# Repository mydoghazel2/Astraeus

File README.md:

# Astraeus

This is the github repo of an SRAD avionics project named Astraeus.

Astreaus is a student led project to develop cheap, open-source, and modular avionics. The goal is to create electronics for our competition rocket and for student use on personal rockets. 

Astraeus is the greek god of the wind and dusk

# Final Design 
## Top Side

## Bottom Side 

# PCB

EAGLE is used as the PCB designing software. All the libraries needed is included in `./PCB/lib`

- if you are on linux. Use the following command to make a sim links to the default eagle save directory  

```
cd ~/EAGLE/projects
ln -s ~/Projects/Astraeus/PCB/ git-pcb
```

- if you are on windows 10: Add instructions on how to get EAGLE running

# TO-DO

- [x] Initial planning and requirement gathering.
- [x] Finalizing the hardware specification.
- [x] Schematic design
  - [x] BMS
  - [x] voltage regulation
  - [x] Sensors
  - [x] USB
  - [ ] upload/download
  - [ ] SD card

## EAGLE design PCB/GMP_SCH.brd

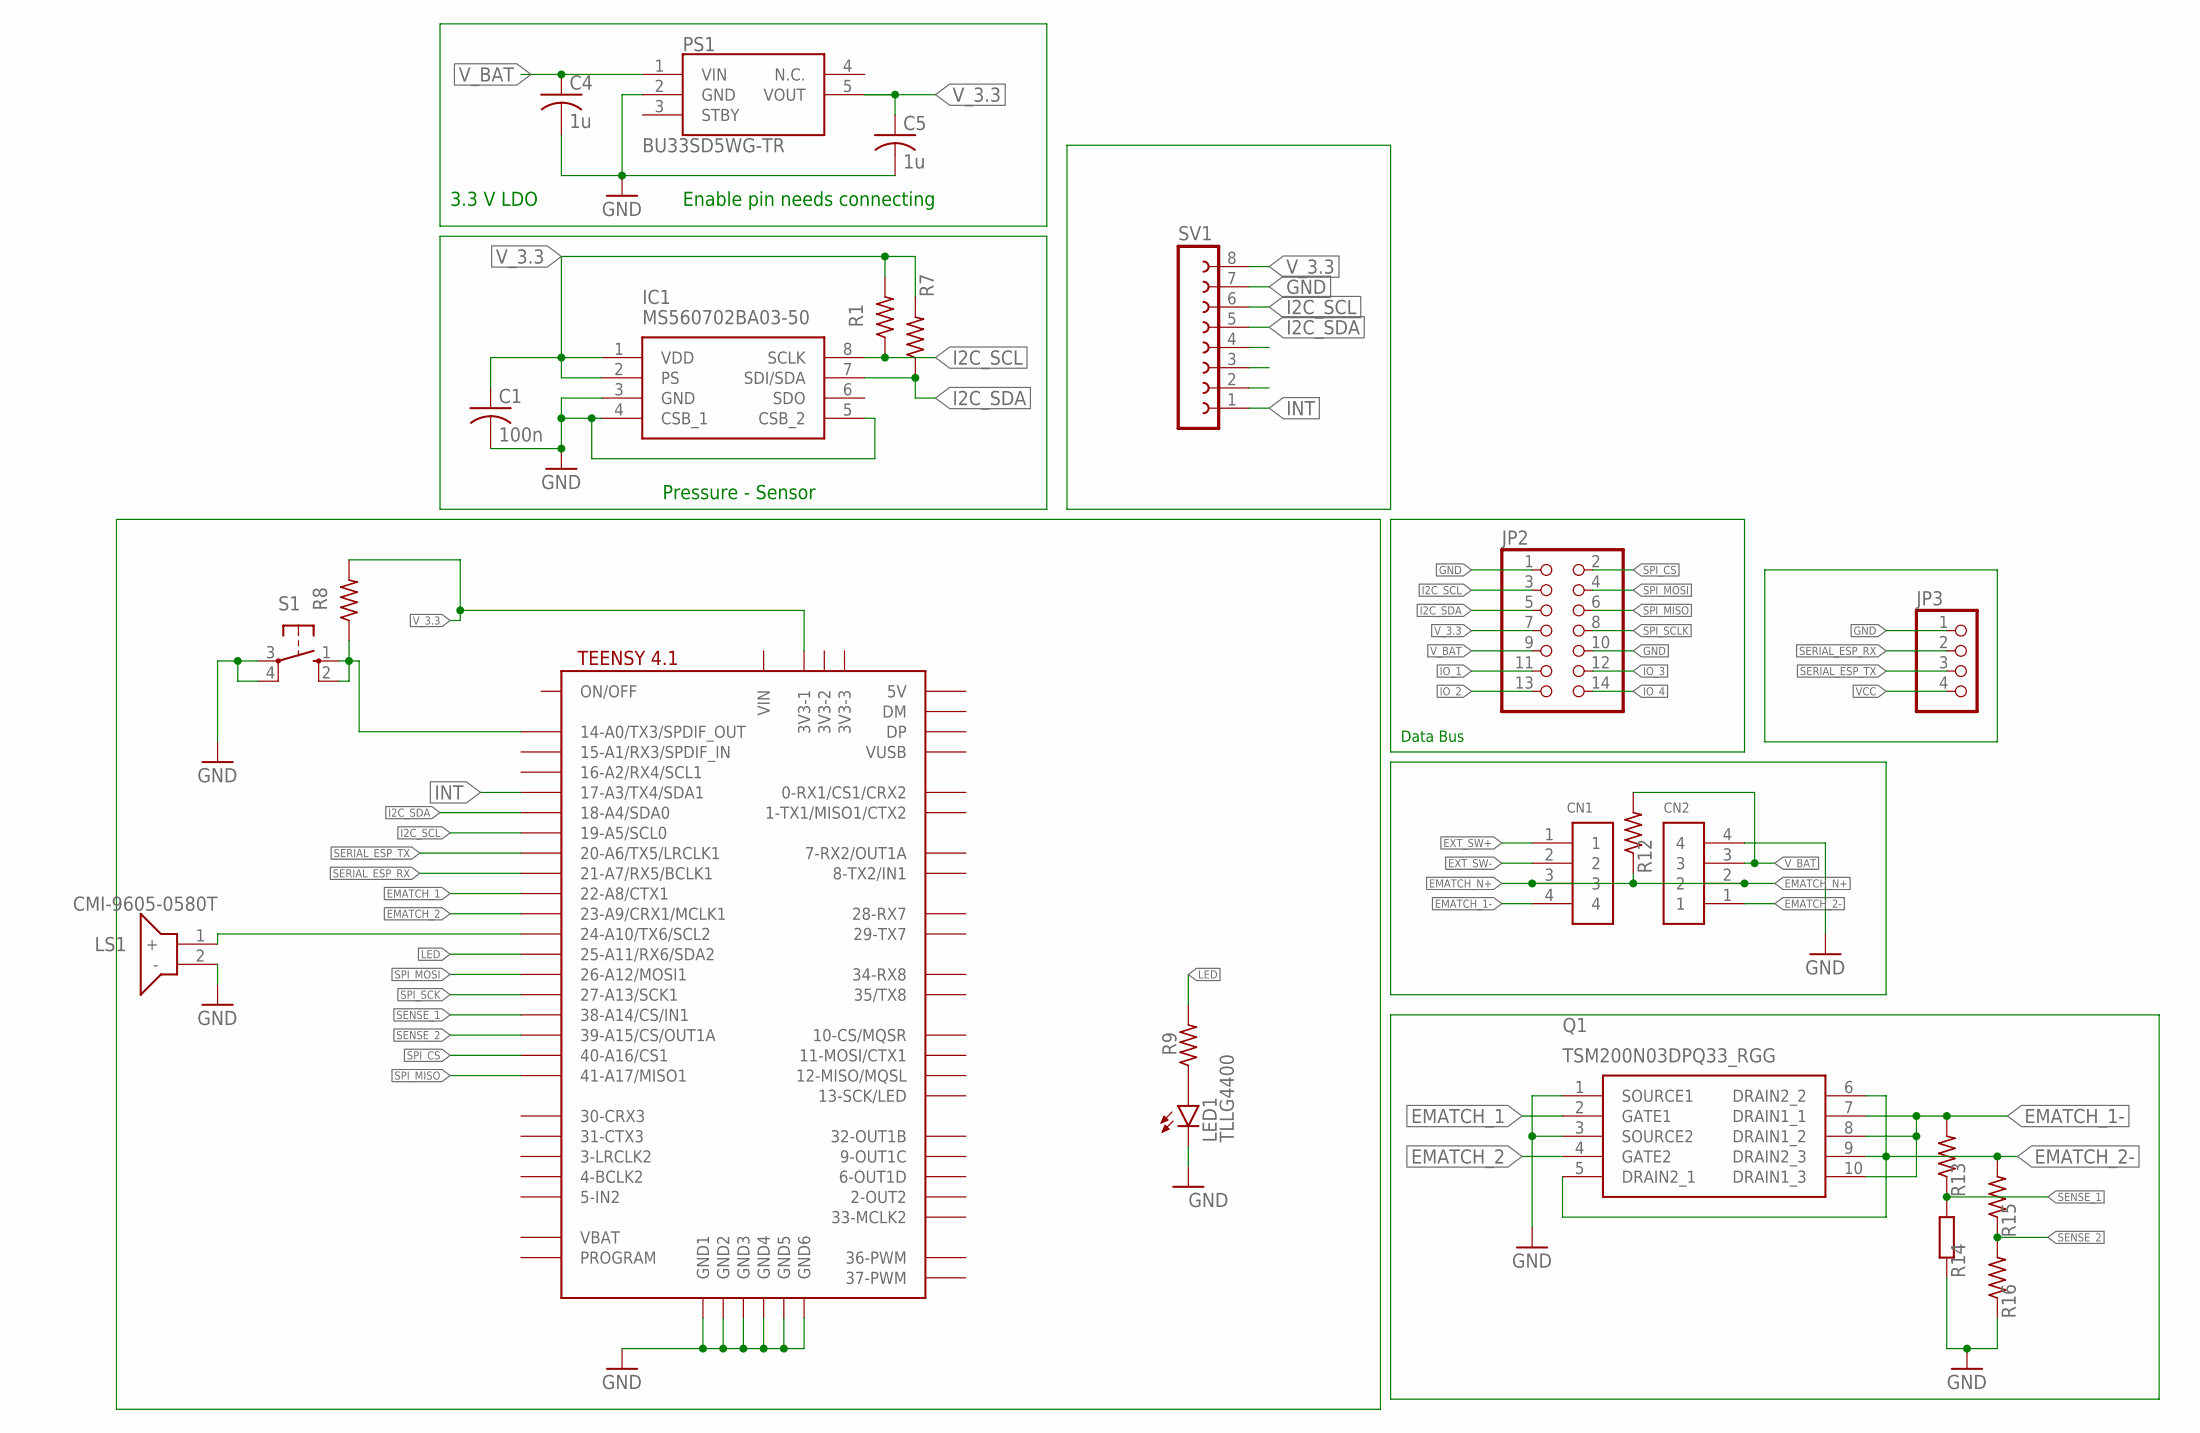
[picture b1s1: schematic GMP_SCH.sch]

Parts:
C1: 100n; C0805
C4, C5: 1u; C0805
CN1, CN2: 1X4-3.5MM; 1X04-3.5MM
IC1: MS560702BA03-50; MS5607-02BA03
JP2: PINHD-2X7; 2X07
JP3: PINHD-1X4/90; 1X04/90
LED1: TLLG4400; LED3MM
LS1: CMI-9605-0580T; CMI96050580T
PS1: BU33SD5WG-TR; SOT95P280X125-5N
Q1: TSM200N03DPQ33_RGG; TSM200N03DPQ33RGG
R1, R7, R8: 10k; 0805-THM
R9: 2k; 0805-THM
R12: 0; 0805-THM
R13, R15: 100k; 0805-THM
R14: 27k; 0207/12
R16: 27k; 0805-THM
S1: 10-XX; B3F-10XX
SV1: FE08-1; FE08
U$1: TEENSY41-E; TENNSY41-E

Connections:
EMATCH_1: Q1.2 (GATE1), U$1.22-A8/CTX1
EMATCH_1-: CN1.4, Q1.7 (DRAIN1_1), Q1.8 (DRAIN1_2), Q1.10 (DRAIN1_3), R13.2
EMATCH_2: Q1.4 (GATE2), U$1.23-A9/CRX1/MCLK1
EMATCH_2-: CN2.1, Q1.5 (DRAIN2_1), Q1.6 (DRAIN2_2), Q1.9 (DRAIN2_3), R15.2
EMATCH_N+: CN1.3, CN2.2, R12.1
EXT_SW+: CN1.1
EXT_SW-: CN1.2
GND: C1.2, C4.2, C5.2, CN2.4, IC1.3 (GND), IC1.4 (CSB_1), IC1.5 (CSB_2), JP2.1, JP2.10, JP3.1, LED1.K (C), LS1.2 (-), PS1.2 (GND), Q1.1 (SOURCE1), Q1.3 (SOURCE2), R14.1, R16.1, S1.3, S1.4 (P1), SV1.7, U$1.GND1, U$1.GND2, U$1.GND3, U$1.GND4, U$1.GND5, U$1.GND6
I2C_SCL: IC1.8 (SCLK), JP2.3, R1.1, SV1.6, U$1.19-A5/SCL0
I2C_SDA: IC1.7 (SDI/SDA), JP2.5, R7.1, SV1.5, U$1.18-A4/SDA0
INT: SV1.1, U$1.17-A3/TX4/SDA1, U$1.30-CRX3
IO_1: JP2.11
IO_2: JP2.13
IO_3: JP2.12
IO_4: JP2.14
LED: R9.2, U$1.25-A11/RX6/SDA2
unnamed: LED1.A, R9.1
unnamed: LS1.1 (+), U$1.24-A10/TX6/SCL2
unnamed: R8.1, S1.1 (S), S1.2 (S1), U$1.14-A0/TX3/SPDIF_OUT
SENSE_1: R13.1, R14.2, U$1.38-A14/CS/IN1
SENSE_2: R15.1, R16.2, U$1.39-A15/CS/OUT1A
SERIAL_ESP_RX: JP3.2, U$1.21-A7/RX5/BCLK1
SERIAL_ESP_TX: JP3.3, U$1.20-A6/TX5/LRCLK1
SPI_CS: JP2.2, U$1.40-A16/CS1
SPI_MISO: JP2.6, U$1.41-A17/MISO1
SPI_MOSI: JP2.4, U$1.26-A12/MOSI1
SPI_SCK: U$1.27-A13/SCK1
SPI_SCLK: JP2.8
VCC: JP3.4
V_3.3: C1.1, C5.1, IC1.1 (VDD), IC1.2 (PS), JP2.7, PS1.5 (VOUT), R1.2, R7.2, R8.2, SV1.8, U$1.3V3-1
V_BAT: C4.1, CN2.3, JP2.9, PS1.1 (VIN), R12.2

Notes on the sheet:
Pressure - Sensor
Enable pin needs connecting
3.3 V LDO
Data Bus

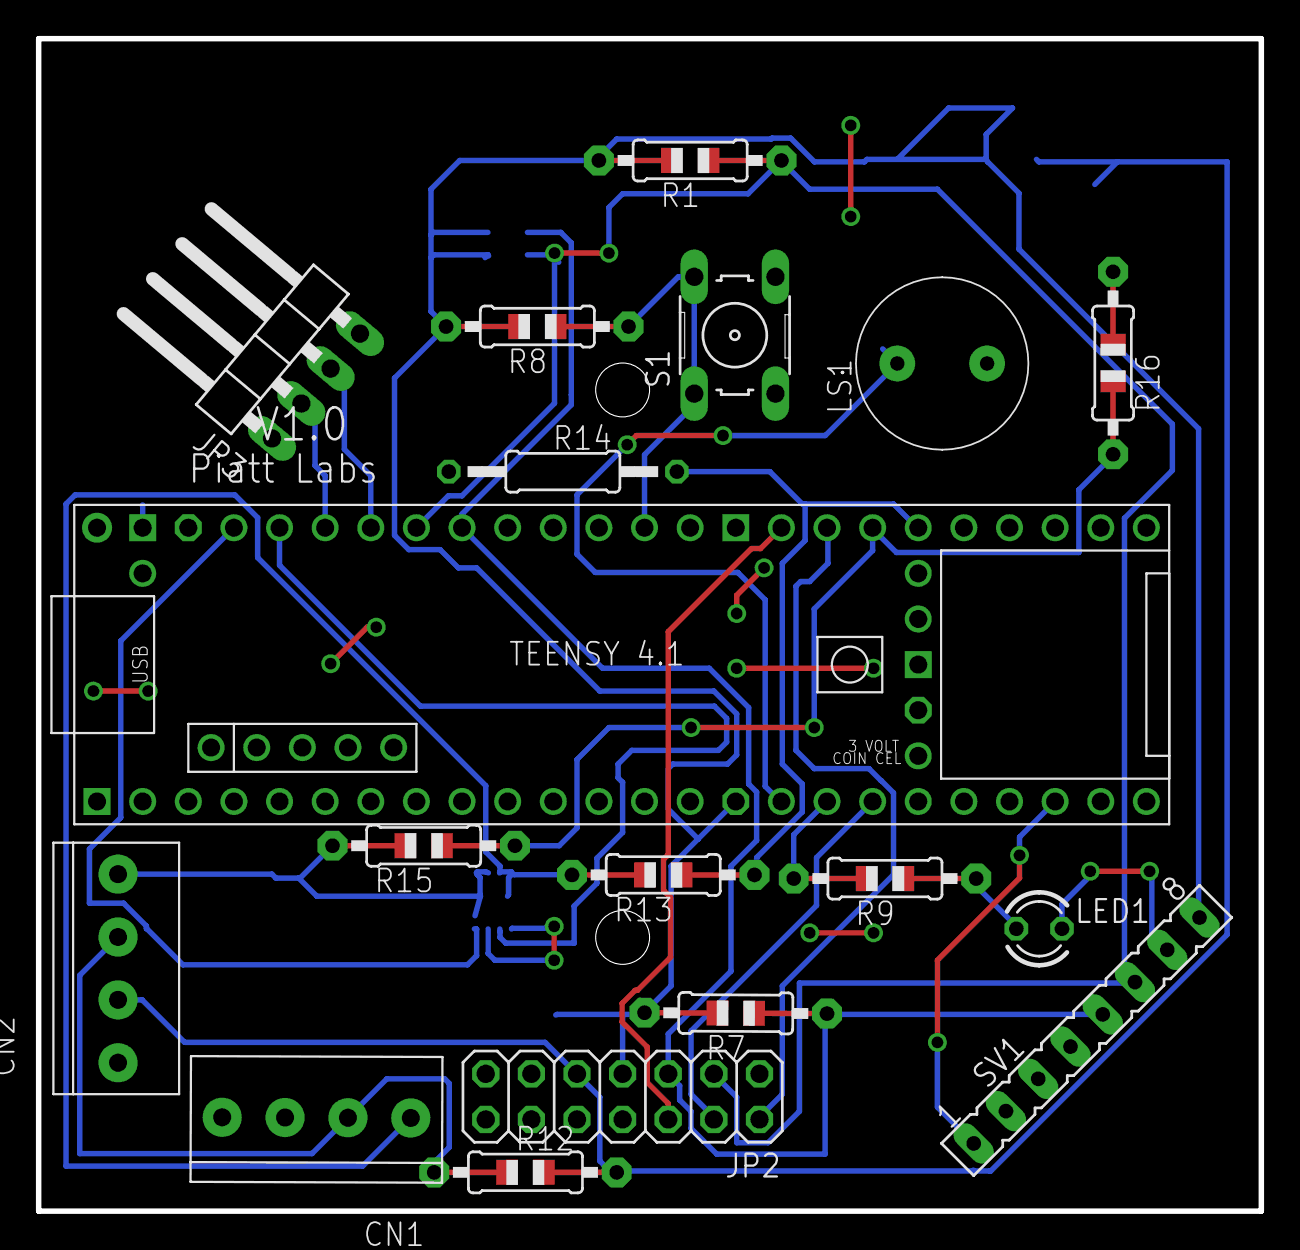
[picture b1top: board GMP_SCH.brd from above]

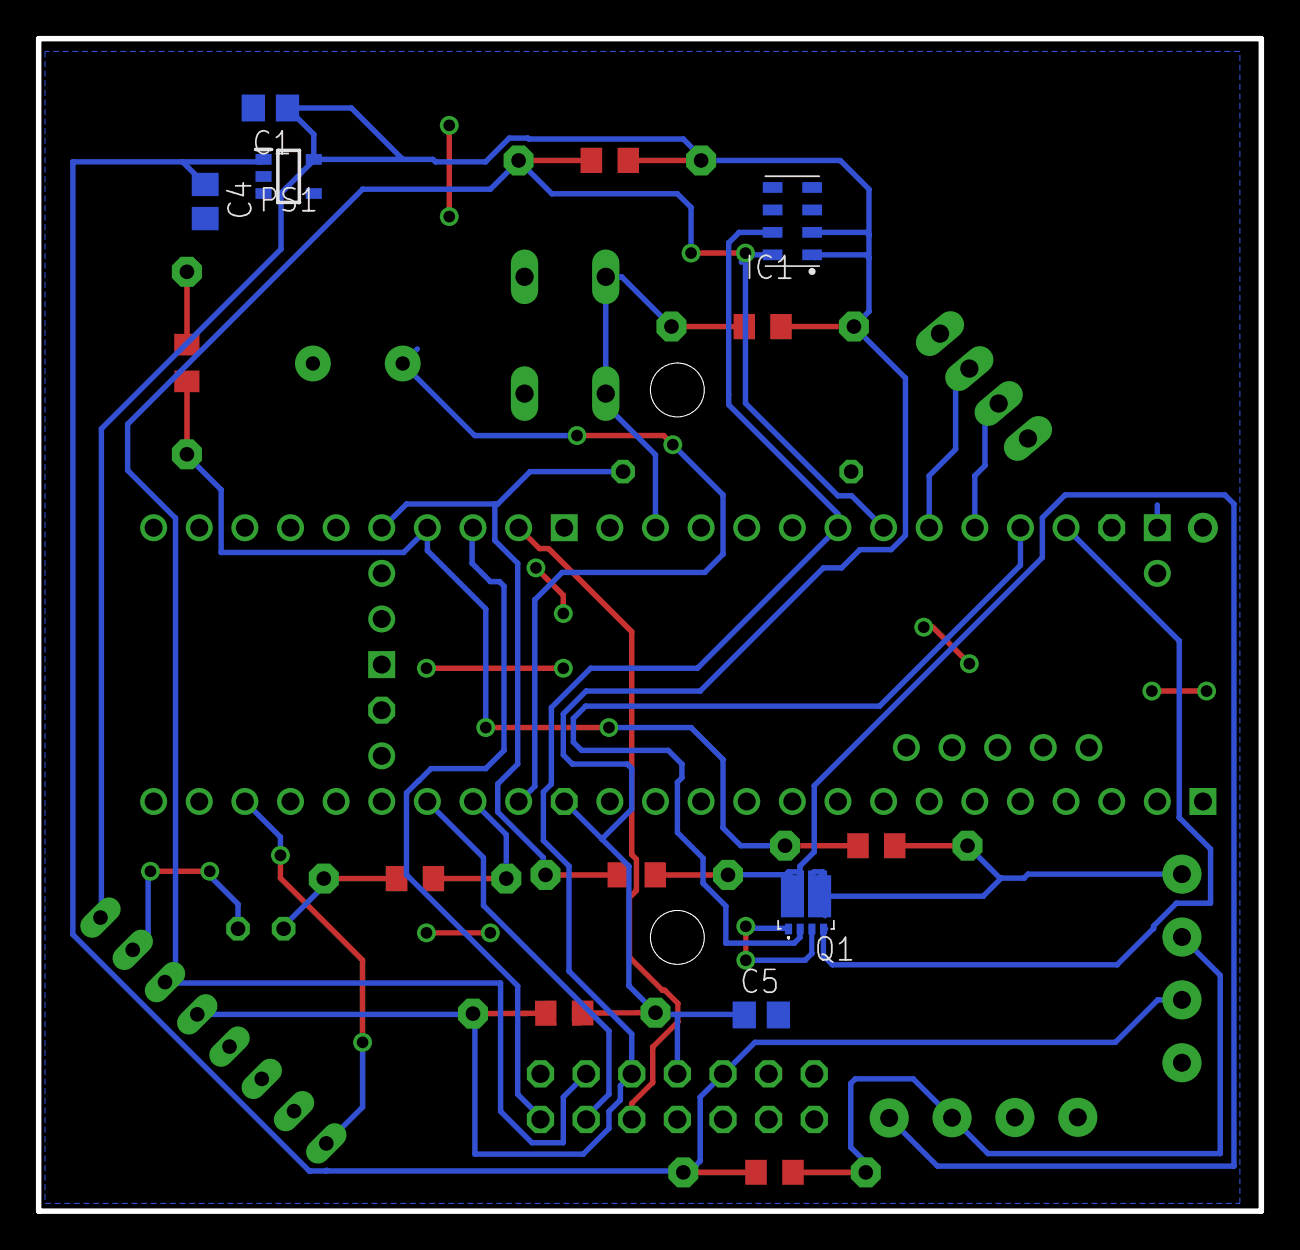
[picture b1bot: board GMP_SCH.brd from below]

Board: 2 copper layers, 68.1 x 65.3 mm, 24 parts (6 on the bottom side), 22 nets.

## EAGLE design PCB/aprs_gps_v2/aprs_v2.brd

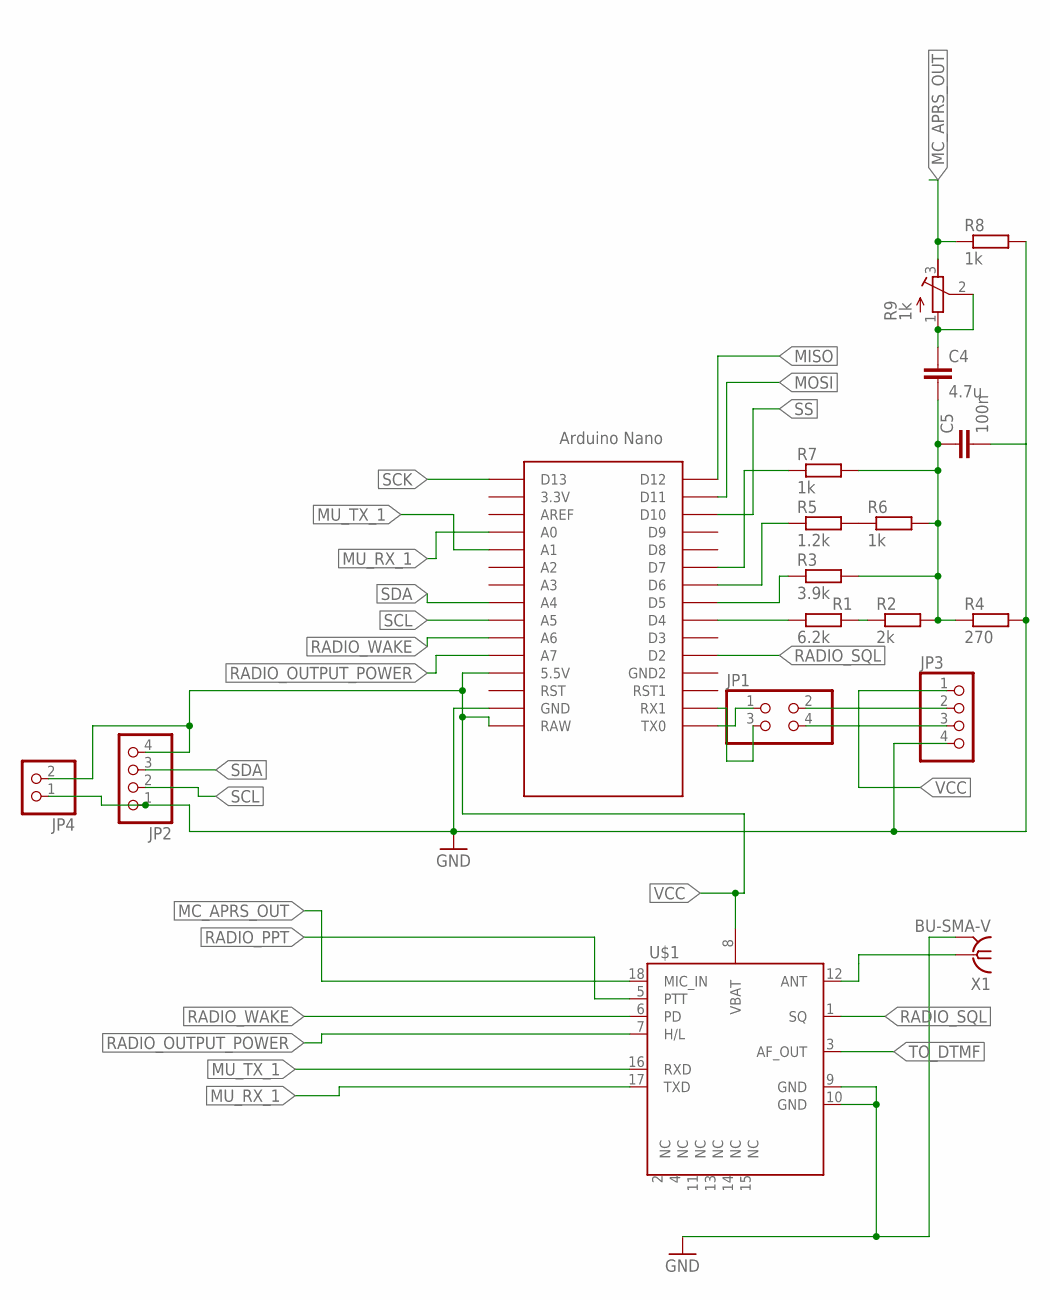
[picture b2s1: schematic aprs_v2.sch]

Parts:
C4: 4.7u; C1206
C5: 100n; C0805
JP1: PINHD-2X2; 2X02
JP2, JP3: PINHD-1X4; 1X04
JP4: PINHD-1X2; 1X02
R1: 6.2k; 0207/7
R2: 2k; 0207/7
R3: 3.9k; 0207/7
R4: 270; 0204/7
R5: 1.2k; 0207/7
R6: 1k; 0207/7
R7: 1k; 0204/5
R8: 1k; 0207/12
R9: 1k; RTRIM3339P
U$1: DRA818A
U$2: NANO
X1: BU-SMA-V

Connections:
GND: C5.2, JP2.1, JP3.4, JP4.1, R4.2, R8.2, U$1.9 (GND), U$1.10 (GND), U$2.GND, X1.2, X1.3 (2), X1.4 (2), X1.5 (2)
MC_APRS_OUT: R8.1, R9.3 (E), U$1.18 (MIC_IN)
MISO: U$2.D12
MOSI: U$2.D11
MU_RX_1: U$1.17 (TXD), U$2.A0
MU_TX_1: U$1.16 (RXD), U$2.A1
unnamed: U$1.12 (ANT), X1.1
unnamed: JP1.1, U$2.TX0
unnamed: JP1.2, JP3.2
unnamed: R1.1, U$2.D4
unnamed: R3.1, U$2.D5
unnamed: R5.1, U$2.D6
unnamed: R7.1, U$2.D7
unnamed: R1.2, R2.1
unnamed: R5.2, R6.1
unnamed: C4.2, C5.1, R2.2, R3.2, R4.1, R6.2, R7.2
unnamed: C4.1, R9.1 (A), R9.2 (S)
unnamed: JP1.3, U$2.RX1
unnamed: JP1.4, JP3.3
RADIO_OUTPUT_POWER: U$1.7 (H/L), U$2.A7
RADIO_PPT: U$1.5 (PTT)
RADIO_SQL: U$1.1 (SQ), U$2.D2
RADIO_WAKE: U$1.6 (PD), U$2.A6
SCK: U$2.D13
SCL: JP2.2, U$2.A5
SDA: JP2.3, U$2.A4
SS: U$2.D10
TO_DTMF: U$1.3 (AF_OUT)
VCC: JP2.4, JP3.1, JP4.2, U$1.8 (VBAT), U$2.5V (5.5V), U$2.RAW

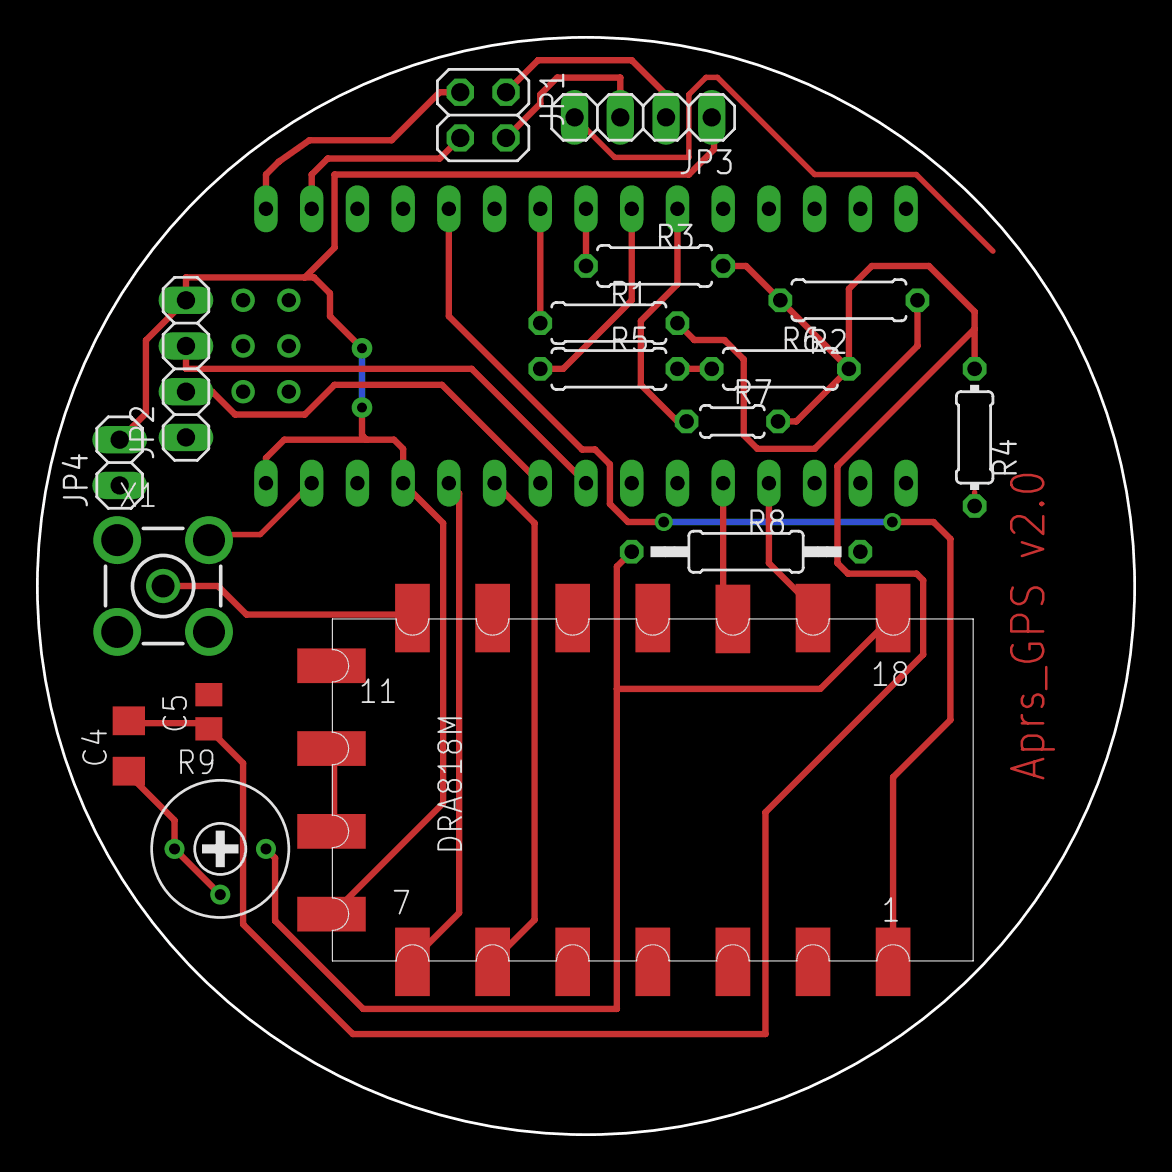
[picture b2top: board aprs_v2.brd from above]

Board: 2 copper layers, 61.0 x 61.0 mm, 18 parts (1 on the bottom side), 23 nets.

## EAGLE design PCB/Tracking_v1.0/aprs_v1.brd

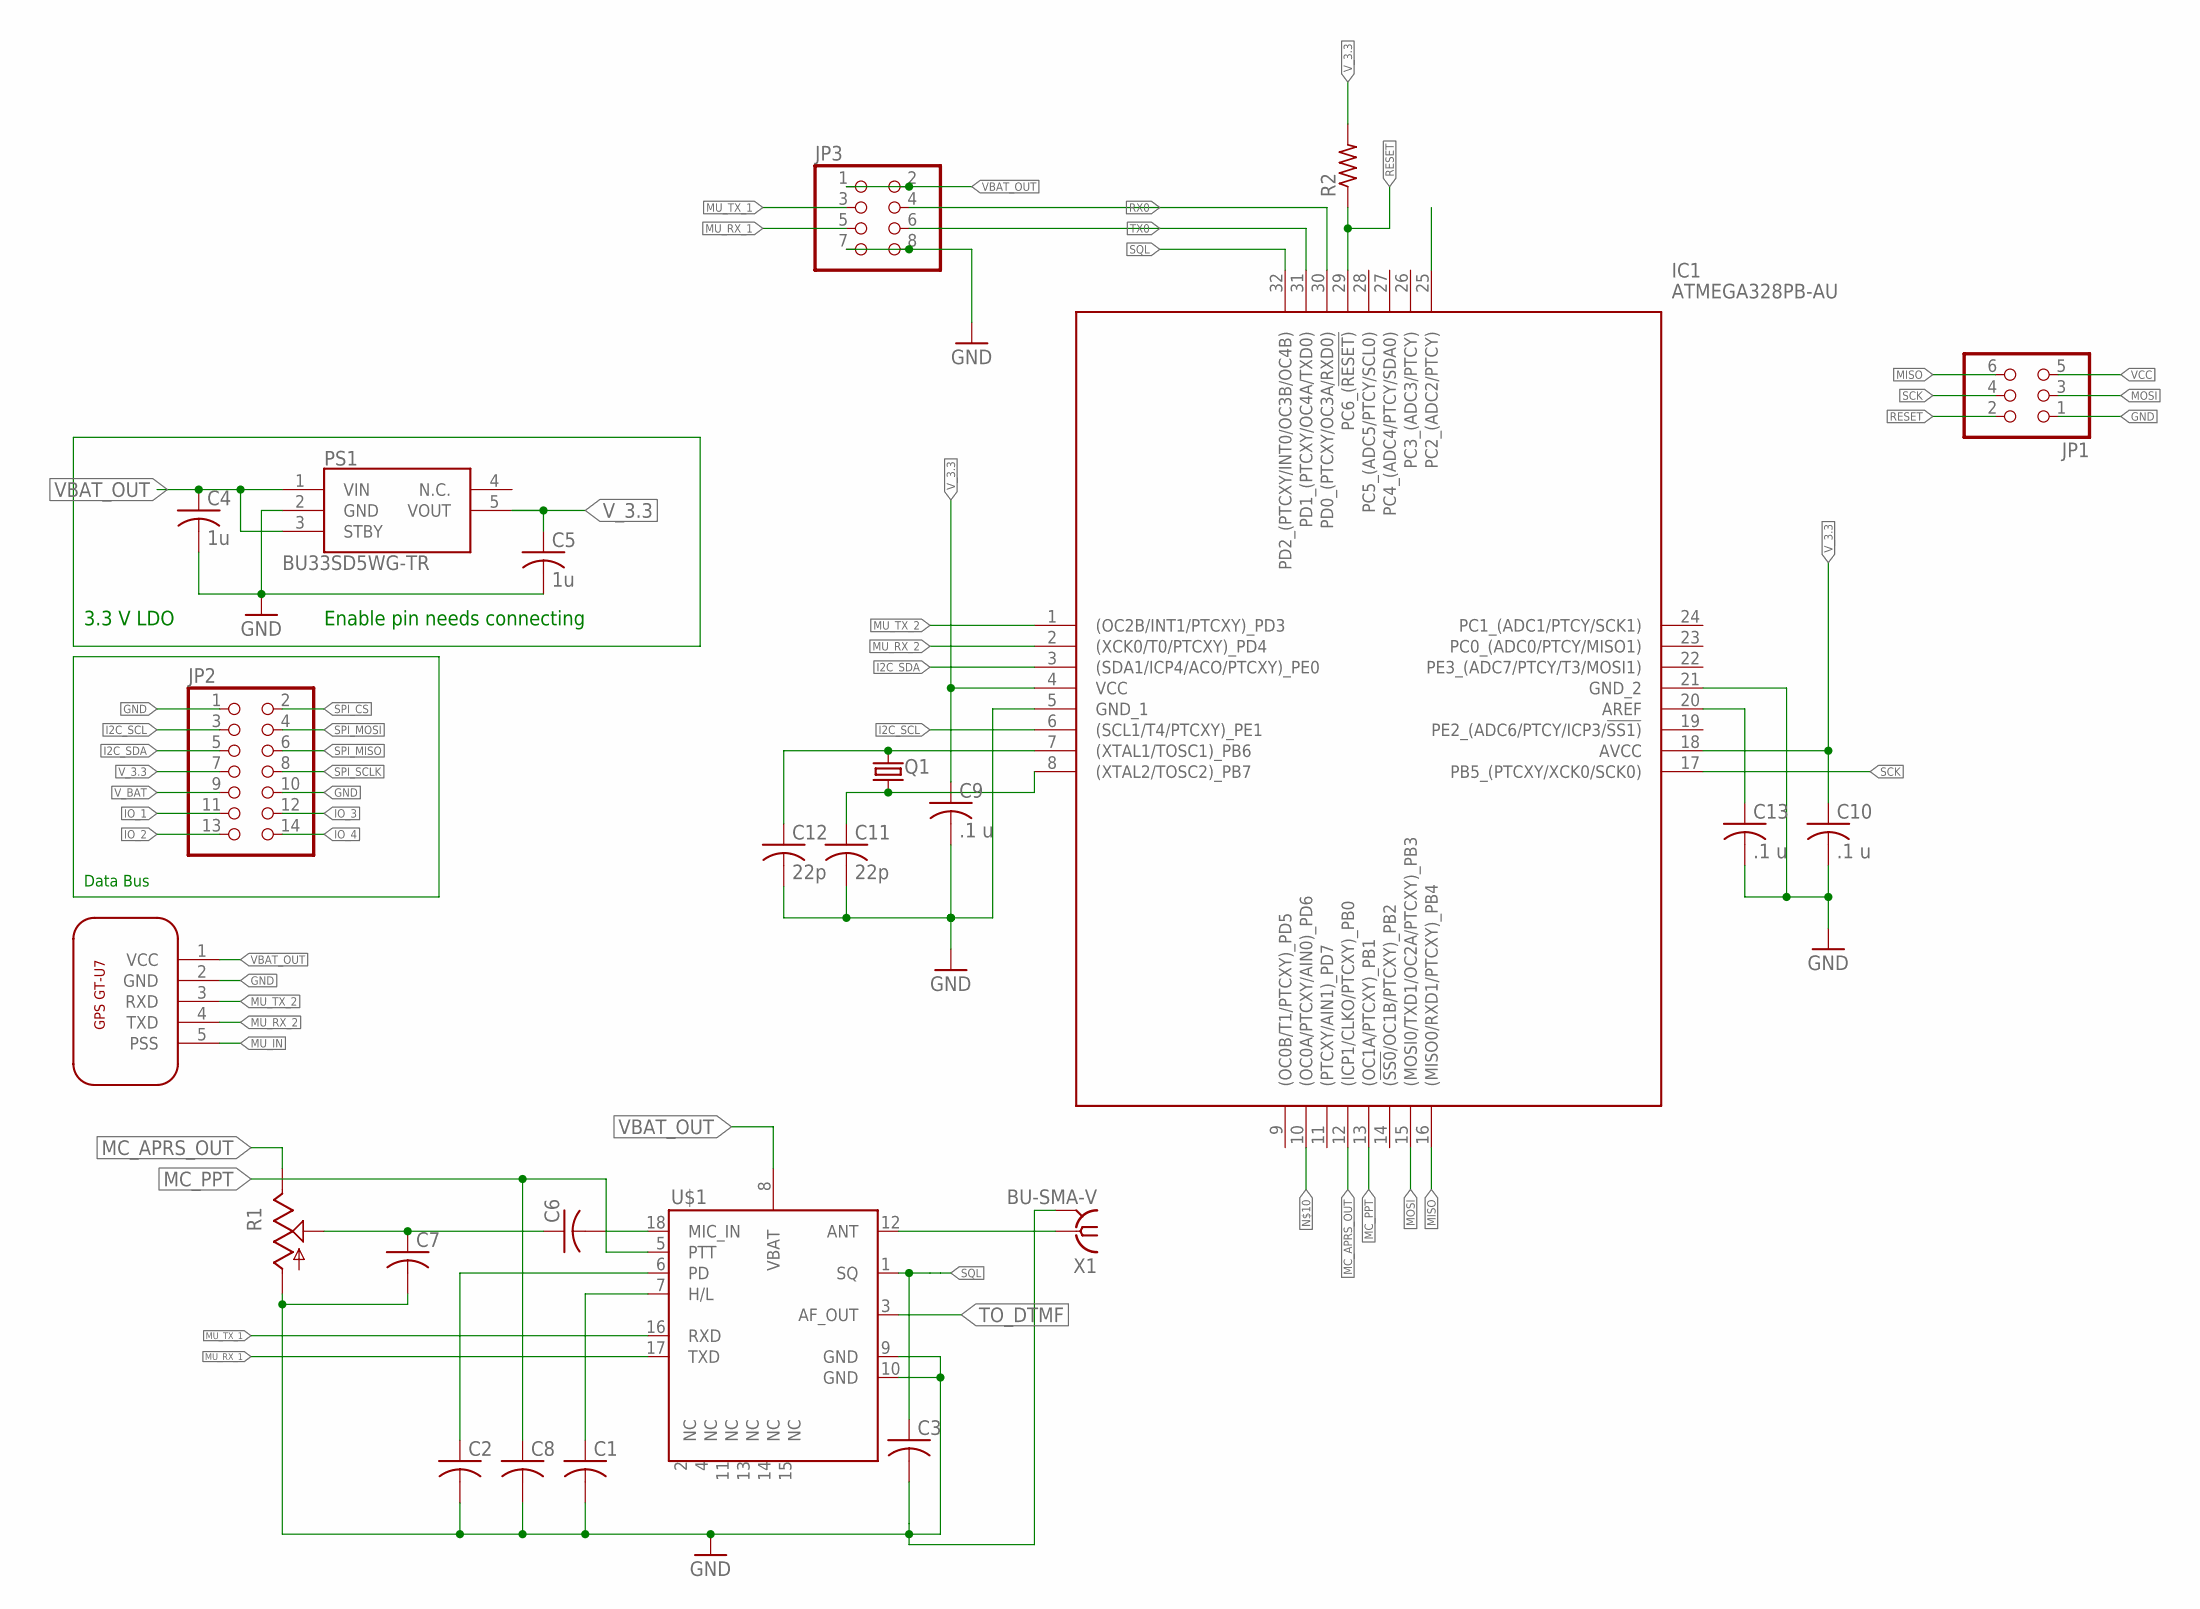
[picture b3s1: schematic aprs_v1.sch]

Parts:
C1, C2, C3, C6, C7, C8: C-USC0805; C0805
C4, C5: 1u; C0805
C9, C10, C13: .1 u; C0805
C11, C12: 22p; C0805
IC1: ATMEGA328PB-AU; QFP80P900X900X120-32N
JP1: PINHD-2X3; 2X03
JP2: PINHD-2X7; 2X07
JP3: PINHD-2X4; 2X04
PS1: BU33SD5WG-TR; SOT95P280X125-5N
Q1: CRYSTALHC49S; HC49/S
R1: TRIM_US-CA6V; CA6V
R2: R-US_M0805; M0805
U$1: DRA818A
U$2: GT-U7; GPS_AHE
X1: BU-SMA-V

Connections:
GND: C1.2, C2.2, C3.2, C4.2, C5.2, C7.2, C8.2, C9.2, C10.2, C11.2, C12.2, C13.2, IC1.5 (GND_1), IC1.21 (GND_2), JP1.1, JP2.1, JP2.10, JP3.7, JP3.8, PS1.2 (GND), R1.A, U$1.9 (GND), U$1.10 (GND), U$2.2 (GND), X1.2, X1.3 (2), X1.4 (2), X1.5 (2)
I2C_SCL: IC1.6 ((SCL1/T4/PTCXY)_PE1), JP2.3
I2C_SDA: IC1.3 ((SDA1/ICP4/ACO/PTCXY)_PE0), JP2.5
IO_1: JP2.11
IO_2: JP2.13
IO_3: JP2.12
IO_4: JP2.14
MC_APRS_OUT: IC1.12 ((ICP1/CLKO/PTCXY)_PB0), R1.E
MC_PPT: C8.1, IC1.13 ((OC1A/PTCXY)_PB1), U$1.5 (PTT)
MISO: IC1.16 ((MISO0/RXD1/PTCXY)_PB4), JP1.6
MOSI: IC1.15 ((MOSI0/TXD1/OC2A/PTCXY)_PB3), JP1.3
MU_IN: U$2.5 (PSS)
MU_RX_1: JP3.5, U$1.17 (TXD)
MU_RX_2: IC1.2 ((XCK0/T0/PTCXY)_PD4), U$2.4 (TXD)
MU_TX_1: JP3.3, U$1.16 (RXD)
MU_TX_2: IC1.1 ((OC2B/INT1/PTCXY)_PD3), U$2.3 (RXD)
unnamed: C2.1, U$1.6 (PD)
unnamed: C1.1, U$1.7 (H/L)
unnamed: U$1.12 (ANT), X1.1
unnamed: C6.2, U$1.18 (MIC_IN)
unnamed: C13.1, IC1.20 (AREF)
unnamed: C6.1, C7.1, R1.S
unnamed: C12.1, IC1.7 ((XTAL1/TOSC1)_PB6), Q1.2
unnamed: C11.1, IC1.8 ((XTAL2/TOSC2)_PB7), Q1.1
RESET: IC1.29 (PC6_(!RESET)), JP1.2, R2.1
RX0: IC1.30 (PD0_(PTCXY/OC3A/RXD0)), JP3.4
SCK: IC1.17 (PB5_(PTCXY/XCK0/SCK0)), JP1.4
SPI_CS: JP2.2
SPI_MISO: JP2.6
SPI_MOSI: JP2.4
SPI_SCLK: JP2.8
SQL: C3.1, IC1.32 (PD2_(PTCXY/INT0/OC3B/OC4B)), U$1.1 (SQ)
TO_DTMF: U$1.3 (AF_OUT)
TX0: IC1.31 (PD1_(PTCXY/OC4A/TXD0)), JP3.6
VBAT_OUT: C4.1, JP3.1, JP3.2, PS1.1 (VIN), PS1.3 (STBY), U$1.8 (VBAT), U$2.1 (VCC)
VCC: JP1.5
V_3.3: C5.1, C9.1, C10.1, IC1.4 (VCC), IC1.18 (AVCC), JP2.7, PS1.5 (VOUT), R2.2
V_BAT: JP2.9

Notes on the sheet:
Data Bus
Enable pin needs connecting
3.3 V LDO

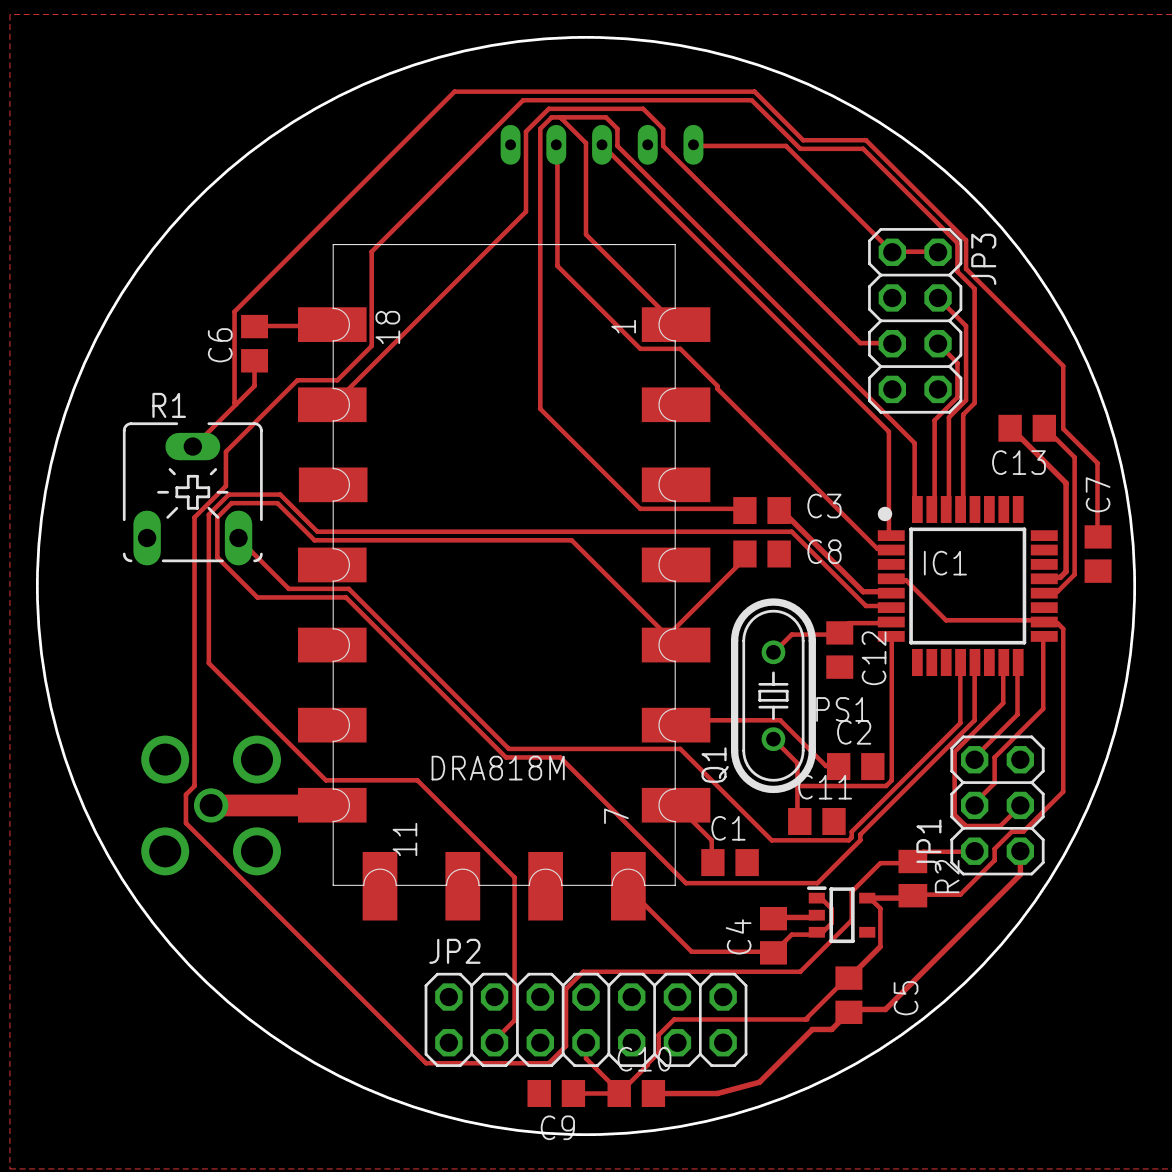
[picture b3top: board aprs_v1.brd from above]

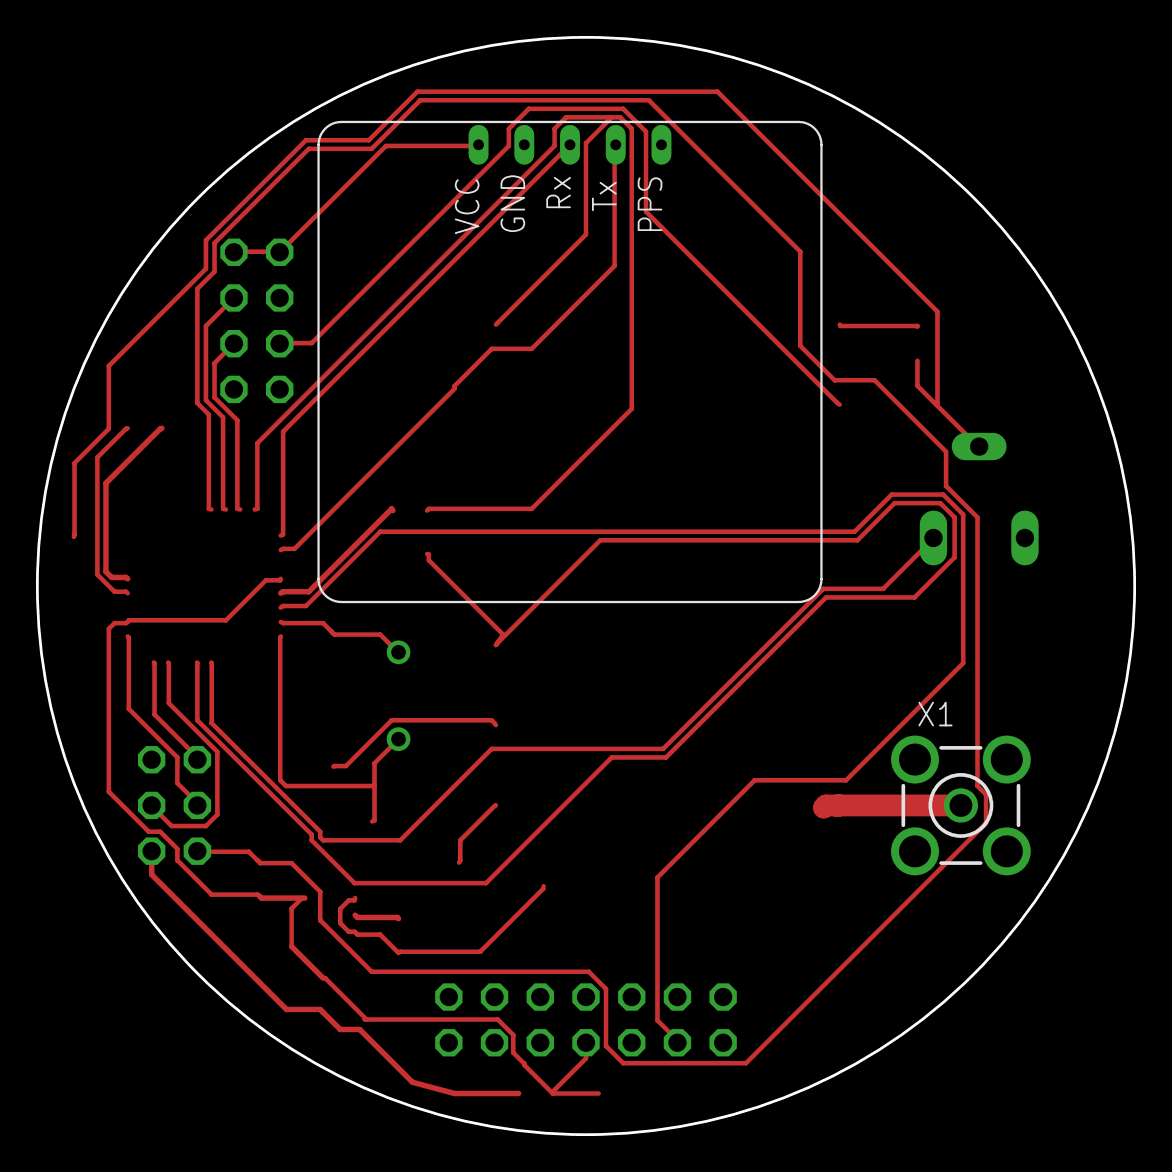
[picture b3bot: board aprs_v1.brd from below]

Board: 2 copper layers, 61.0 x 61.0 mm, 24 parts (2 on the bottom side), 26 nets.

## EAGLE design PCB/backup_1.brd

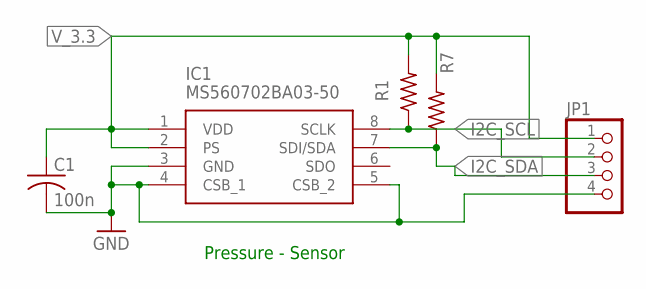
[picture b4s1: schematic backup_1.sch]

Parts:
C1: 100n; C050-024X044
IC1: MS560702BA03-50; MS5607-02BA03
JP1: PINHD-1X4; 1X04
R1, R7: 10k; 0204/7

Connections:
GND: C1.2, IC1.3 (GND), IC1.4 (CSB_1), IC1.5 (CSB_2), JP1.4
I2C_SCL: IC1.8 (SCLK), JP1.2, R1.1
I2C_SDA: IC1.7 (SDI/SDA), JP1.3, R7.1
V_3.3: C1.1, IC1.1 (VDD), IC1.2 (PS), JP1.1, R1.2, R7.2

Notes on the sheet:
Pressure - Sensor

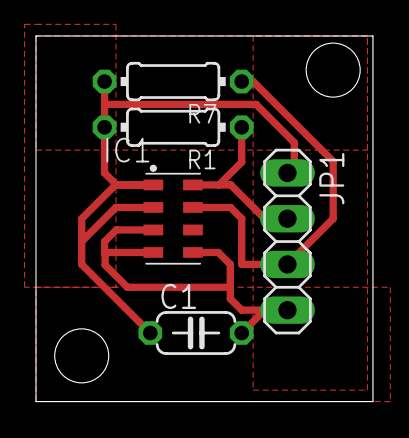
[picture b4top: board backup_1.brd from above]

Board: 2 copper layers, 18.7 x 20.3 mm, 5 parts (0 on the bottom side), 4 nets.
